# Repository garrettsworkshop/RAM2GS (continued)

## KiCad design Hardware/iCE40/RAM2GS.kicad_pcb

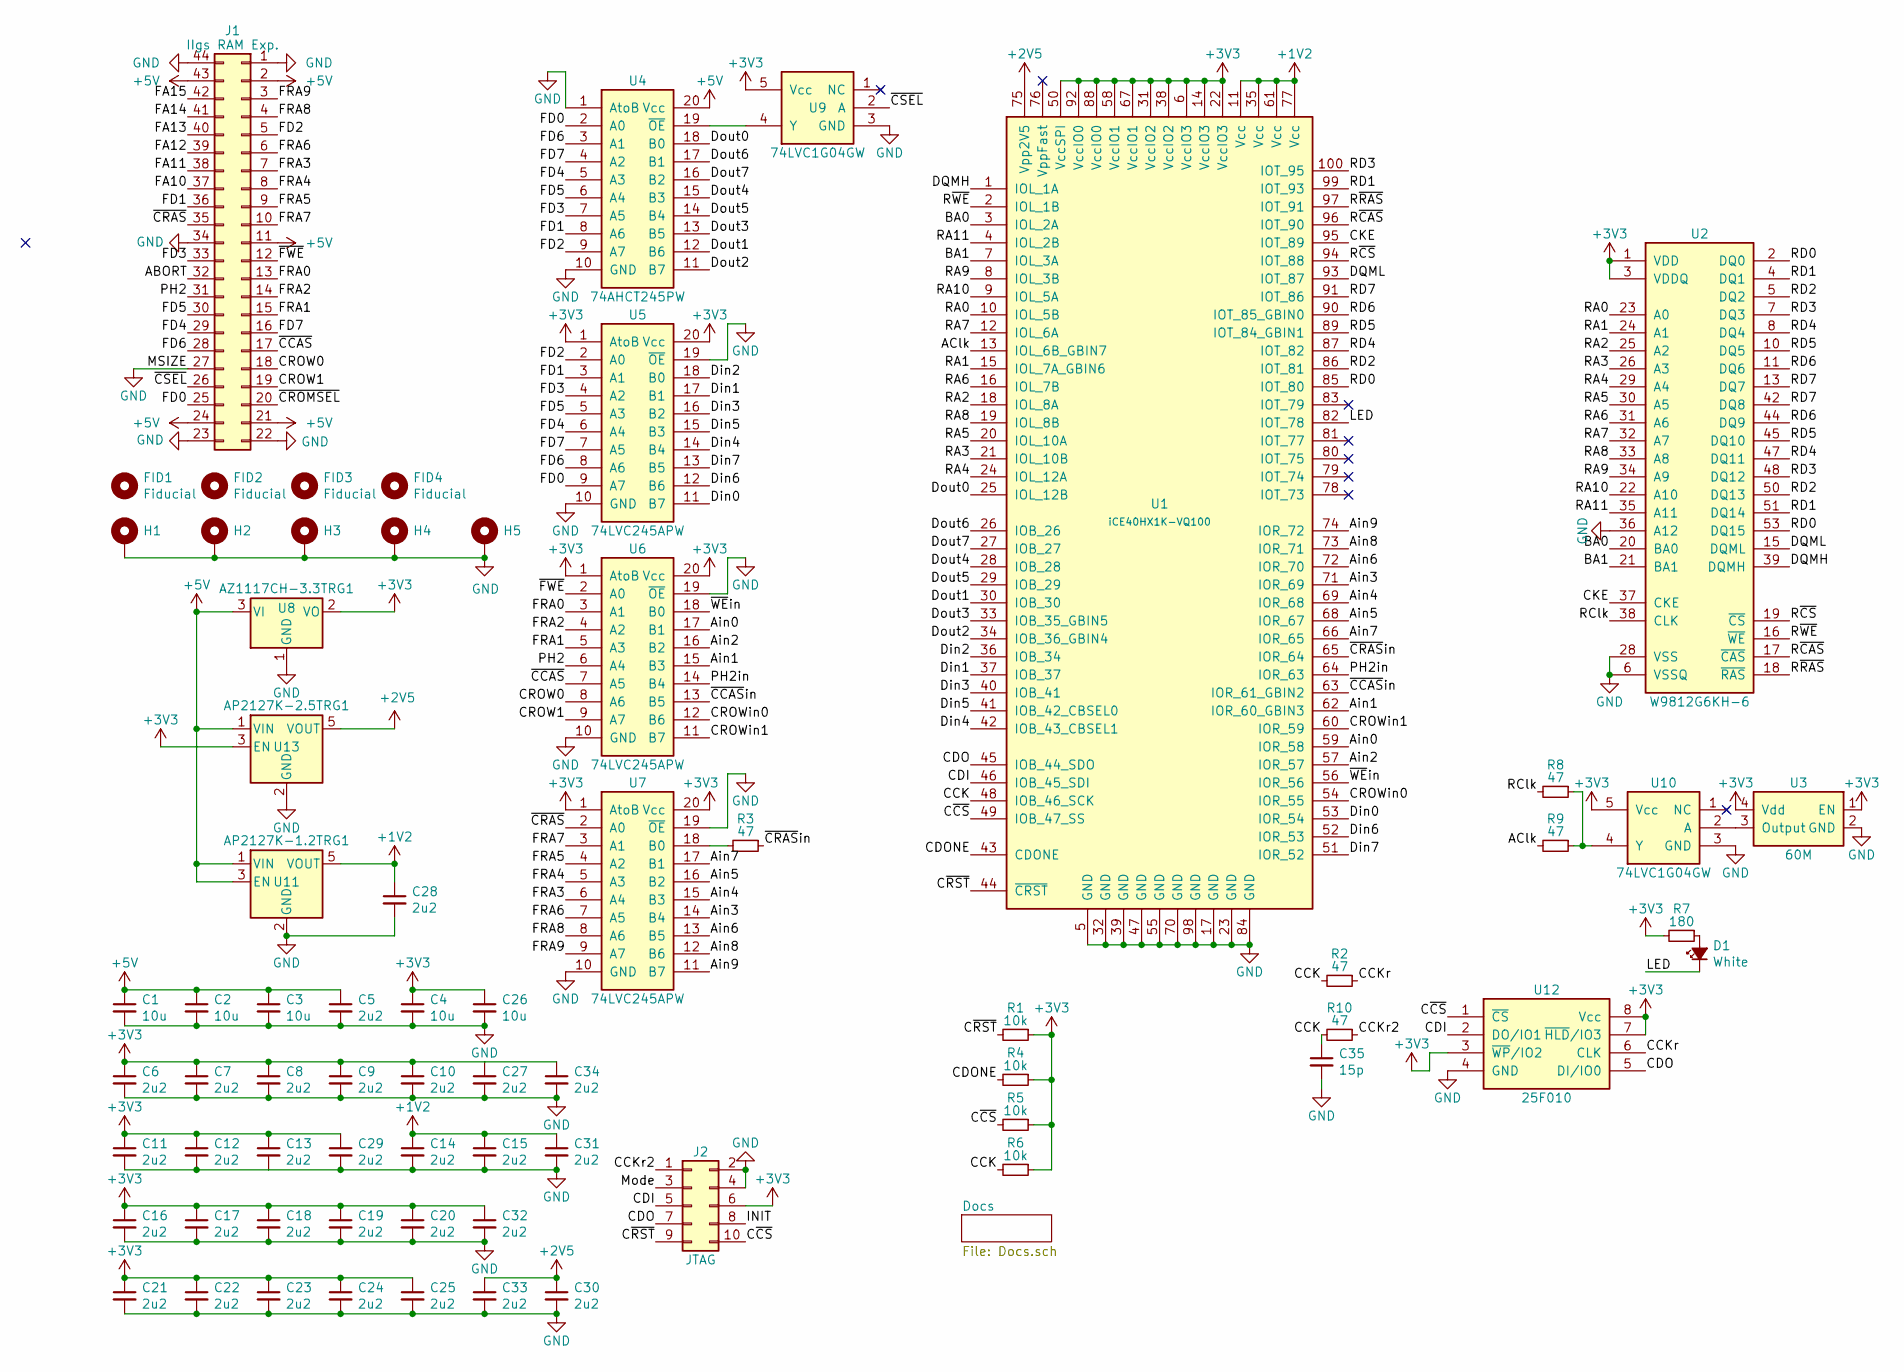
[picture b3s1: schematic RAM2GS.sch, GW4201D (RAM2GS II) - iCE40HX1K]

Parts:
C1, C2, C3, C4, C26: 10u; C_0805; Mfg. Part Numbers Samsung CL21A106KAYNNNE; LCSC Part C15850
C5, C6, C7, C8, C9, C10, C11, C12, C13, C14, C15, C16, C17, C18, C19, C20, C21, C22, C23, C24, C25, C27, C28, C29, C30, C31, C32, C33, C34: 2u2; C_0603; Mfg. Part Numbers Samsung CL10A225KO8NNNC; LCSC Part C23630
C35: 15p; C_0603; Mfg. Part Numbers Samsung CL10C150JB8NNNC; LCSC Part C1644
D1: White; LED_0805; Mfg. Part Numbers Hubei Kento C34499; LCSC Part C34499
FID1, FID2, FID3, FID4: Fiducial
H1, H2, H4, H5: PasteHole_1.152mm_NPTH
H3: PasteHole_1.1mm_PTH
J1: IIgs RAM Exp.; AppleIIgsMemoryExpansion_Edge
J2: JTAG; Tag-Connect_TC2050-IDC-FP_2x05_P1.27mm_Vertical
R1, R4, R5, R6: 10k; R_0603; Mfg. Part Numbers Uniroyal 0603WAF1002T5E; LCSC Part C25804
R2, R3, R8, R9, R10: 47; R_0603; Mfg. Part Numbers Uniroyal 0603WAF470JT5E; LCSC Part C23182
R7: 180; R_0805; Mfg. Part Numbers Uniroyal 0805W8F1800T5E; LCSC Part C25270
U1: iCE40HX1K-VQ100; TQFP-100_14x14mm_P0.5mm; Mfg. Part Numbers Lattice iCE40HX1K-VQ100; LCSC Part C1519043
U2: W9812G6KH-6; TSOP-II-54_22.2x10.16mm_P0.8mm; Mfg. Part Numbers Winbond W9812G6KH-6, Winbond W9812G6KH-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; LCSC Part C62379
U3: 60M; Crystal_SMD_7050-4Pin_7.0x5.0mm_SiTime; Mfg. Part Numbers SiTime SIT1602AI-82-33E-60.000000Y, She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; LCSC Part C26255
U4: 74AHCT245PW; TSSOP-20_4.4x6.5mm_P0.65mm; Mfg. Part Numbers NXP 74AHCT245PW, NXP 74AHCT245APW, TI S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; LCSC Part C173388
U5, U6, U7: 74LVC245APW; TSSOP-20_4.4x6.5mm_P0.65mm; Mfg. Part Numbers NXP 74LVC245APW, TI SN74LVC245APW, NXP 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; LCSC Part C6082
U8: AZ1117CH-3.3TRG1; SOT-223; Mfg. Part Numbers Diodes AZ1117CH-3.3TRG1, Diodes AZ1117E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; LCSC Part C92102
U9, U10: 74LVC1G04GW; SOT-353; Mfg. Part Numbers NXP 74LVC1G04GW, TI SN74LVC1G04DCK; LCSC Part C10237
U11: AP2127K-1.2TRG1; SOT-23-5; Mfg. Part Numbers Diodes AP2127K-1.2TRG1, Torex XC6228D12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; LCSC Part C151376
U12: 25F010; SOIC-8_3.9mm; Mfg. Part Numbers Zetta ZD25WD20BTIGT, Adesto AT25SF081-S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; LCSC Part C2687406
U13: AP2127K-2.5TRG1; SOT-23-5; Mfg. Part Numbers Diodes AP2127K-2.5TRG1, Torex XC6206J25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; LCSC Part C460326

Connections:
+1V2: C14.1, C15.1, C28.1, C31.1, U1.11 (Vcc), U1.35 (Vcc), U1.61 (Vcc), U1.77 (Vcc), U11.5 (VOUT)
+2V5: C30.1, C33.1, U1.75 (Vpp2V5), U13.5 (VOUT)
+3V3: C4.1, C6.1, C7.1, C8.1, C9.1, C10.1, C11.1, C12.1, C13.1, C16.1, C17.1, C18.1, C19.1, C20.1, C21.1, C22.1, C23.1, C24.1, C25.1, C26.1, C27.1, C29.1, C32.1, C34.1, J2.6, R1.1, R4.1, R5.1, R6.1, R7.2, U1.6 (VccIO3), U1.14 (VccIO3), U1.22 (VccIO3), U1.31 (VccIO2), U1.38 (VccIO2), U1.50 (VccSPI), U1.58 (VccIO1), U1.67 (VccIO1), U1.88 (VccIO0), U1.92 (VccIO0), U2.1 (VDD), U2.3 (VDDQ), U2.9 (VDDQ), U2.14 (VDD), U2.27 (VDD), U2.43 (VDDQ), U2.49 (VDDQ), U3.1 (EN), U3.4 (Vdd), U5.1 (AtoB), U5.20 (Vcc), U6.1 (AtoB), U6.20 (Vcc), U7.1 (AtoB), U7.20 (Vcc), U8.2 (VO), U9.5 (Vcc), U10.5 (Vcc), U12.3 (~WP~/IO2), U12.7 (~HLD~/IO3), U12.8 (Vcc), U13.3 (EN)
+5V: C1.1, C2.1, C3.1, C5.1, J1.2, J1.11, J1.21, J1.24, J1.43, U4.20 (Vcc), U8.3 (VI), U11.1 (VIN), U11.3 (EN), U13.1 (VIN)
/ABORT: J1.32
/AClk: R9.2, U1.13 (IOL_6B_GBIN7)
/Ain0: U1.59 (IOR_58), U6.17 (B1)
/Ain1: U1.62 (IOR_60_GBIN3), U6.15 (B3)
/Ain2: U1.57 (IOR_57), U6.16 (B2)
/Ain3: U1.71 (IOR_69), U7.14 (B4)
/Ain4: U1.69 (IOR_68), U7.15 (B3)
/Ain5: U1.68 (IOR_67), U7.16 (B2)
/Ain6: U1.72 (IOR_70), U7.13 (B5)
/Ain7: U1.66 (IOR_65), U7.17 (B1)
/Ain8: U1.73 (IOR_71), U7.12 (B6)
/Ain9: U1.74 (IOR_72), U7.11 (B7)
/BA0: U1.3 (IOL_2A), U2.20 (BA0)
/BA1: U1.7 (IOL_3A), U2.21 (BA1)
/CCK: C35.1, R2.2, R6.2, R10.2, U1.48 (IOB_46_SCK)
/CCKr: R2.1, U12.6 (CLK)
/CCKr2: J2.1, R10.1
/CDI: J2.5, U1.46 (IOB_45_SDI), U12.2 (DO/IO1)
/CDO: J2.7, U1.45 (IOB_44_SDO), U12.5 (DI/IO0)
/CDONE: R4.2, U1.43 (CDONE)
/CKE: U1.95 (IOT_89), U2.37 (CKE)
/CROW0: J1.18, U6.8 (A6)
/CROW1: J1.19, U6.9 (A7)
/CROWin0: U1.54 (IOR_55), U6.12 (B6)
/CROWin1: U1.60 (IOR_59), U6.11 (B7)
/C~CS~: J2.10, R5.2, U1.49 (IOB_47_SS), U12.1 (~CS~)
/C~RST~: J2.9, R1.2, U1.44 (~CRST~)
/DQMH: U1.1 (IOL_1A), U2.39 (DQMH)
/DQML: U1.93 (IOT_87), U2.15 (DQML)
/Din0: U1.53 (IOR_54), U5.11 (B7)
/Din1: U1.37 (IOB_37), U5.17 (B1)
/Din2: U1.36 (IOB_34), U5.18 (B0)
/Din3: U1.40 (IOB_41), U5.16 (B2)
/Din4: U1.42 (IOB_43_CBSEL1), U5.14 (B4)
/Din5: U1.41 (IOB_42_CBSEL0), U5.15 (B3)
/Din6: U1.52 (IOR_53), U5.12 (B6)
/Din7: U1.51 (IOR_52), U5.13 (B5)
/Dout0: U1.25 (IOL_12B), U4.18 (B0)
/Dout1: U1.30 (IOB_30), U4.12 (B6)
/Dout2: U1.34 (IOB_36_GBIN4), U4.11 (B7)
/Dout3: U1.33 (IOB_35_GBIN5), U4.13 (B5)
/Dout4: U1.28 (IOB_28), U4.15 (B3)
/Dout5: U1.29 (IOB_29), U4.14 (B4)
/Dout6: U1.26 (IOB_26), U4.17 (B1)
/Dout7: U1.27 (IOB_27), U4.16 (B2)
/FA10: J1.37
/FA11: J1.38
/FA12: J1.39
/FA13: J1.40
/FA14: J1.41
/FA15: J1.42
/FD0: J1.25, U4.2 (A0), U5.9 (A7)
/FD1: J1.36, U4.8 (A6), U5.3 (A1)
/FD2: J1.5, U4.9 (A7), U5.2 (A0)
/FD3: J1.33, U4.7 (A5), U5.4 (A2)
/FD4: J1.29, U4.5 (A3), U5.6 (A4)
/FD5: J1.30, U4.6 (A4), U5.5 (A3)
/FD6: J1.28, U4.3 (A1), U5.8 (A6)
/FD7: J1.16, U4.4 (A2), U5.7 (A5)
/FRA0: J1.13, U6.3 (A1)
/FRA1: J1.15, U6.5 (A3)
/FRA2: J1.14, U6.4 (A2)
/FRA3: J1.7, U7.6 (A4)
/FRA4: J1.8, U7.5 (A3)
/FRA5: J1.9, U7.4 (A2)
/FRA6: J1.6, U7.7 (A5)
/FRA7: J1.10, U7.3 (A1)
/FRA8: J1.4, U7.8 (A6)
/FRA9: J1.3, U7.9 (A7)
/INIT: J2.8
/LED: D1.1 (K), U1.82 (IOT_78)
/Mode: J2.3
/PH2: J1.31, U6.6 (A4)
/PH2in: U1.64 (IOR_63), U6.14 (B4)
/RA0: U1.10 (IOL_5B), U2.23 (A0)
/RA1: U1.15 (IOL_7A_GBIN6), U2.24 (A1)
/RA2: U1.18 (IOL_8A), U2.25 (A2)
/RA3: U1.21 (IOL_10B), U2.26 (A3)
/RA4: U1.24 (IOL_12A), U2.29 (A4)
/RA5: U1.20 (IOL_10A), U2.30 (A5)
/RA6: U1.16 (IOL_7B), U2.31 (A6)
/RA7: U1.12 (IOL_6A), U2.32 (A7)
/RA8: U1.19 (IOL_8B), U2.33 (A8)
/RA9: U1.8 (IOL_3B), U2.34 (A9)
/RA10: U1.9 (IOL_5A), U2.22 (A10)
/RA11: U1.4 (IOL_2B), U2.35 (A11)
/RClk: R8.2, U2.38 (CLK)
/RD0: U1.85 (IOT_80), U2.2 (DQ0), U2.53 (DQ15)
/RD1: U1.99 (IOT_93), U2.4 (DQ1), U2.51 (DQ14)
/RD2: U1.86 (IOT_81), U2.5 (DQ2), U2.50 (DQ13)
/RD3: U1.100 (IOT_95), U2.7 (DQ3), U2.48 (DQ12)
/RD4: U1.87 (IOT_82), U2.8 (DQ4), U2.47 (DQ11)
/RD5: U1.89 (IOT_84_GBIN1), U2.10 (DQ5), U2.45 (DQ10)
/RD6: U1.90 (IOT_85_GBIN0), U2.11 (DQ6), U2.44 (DQ9)
/RD7: U1.91 (IOT_86), U2.13 (DQ7), U2.42 (DQ8)
/R~CAS~: U1.96 (IOT_90), U2.17 (~CAS~)
/R~CS~: U1.94 (IOT_88), U2.19 (~CS~)
/R~RAS~: U1.97 (IOT_91), U2.18 (~RAS~)
/R~WE~: U1.2 (IOL_1B), U2.16 (~WE~)
/~CCAS~: J1.17, U6.7 (A5)
/~CCAS~in: U1.63 (IOR_61_GBIN2), U6.13 (B5)
/~CRAS~: J1.35, U7.2 (A0)
/~CRAS~in: R3.1, U1.65 (IOR_64)
/~CROMSEL~: J1.20
/~CSEL~: J1.26, U9.2 (A)
/~FWE~: J1.12, U6.2 (A0)
/~WE~in: U1.56 (IOR_56), U6.18 (B0)
GND: C1.2, C2.2, C3.2, C4.2, C5.2, C6.2, C7.2, C8.2, C9.2, C10.2, C11.2, C12.2, C13.2, C14.2, C15.2, C16.2, C17.2, C18.2, C19.2, C20.2, C21.2, C22.2, C23.2, C24.2, C25.2, C26.2, C27.2, C28.2, C29.2, C30.2, C31.2, C32.2, C33.2, C34.2, C35.2, H1.1, H2.1, H3.1, H4.1, H5.1, J1.1, J1.22, J1.23, J1.27, J1.34, J1.44, J2.2, J2.4, U1.5 (GND), U1.17 (GND), U1.23 (GND), U1.32 (GND), U1.39 (GND), U1.47 (GND), U1.55 (GND), U1.70 (GND), U1.84 (GND), U1.98 (GND), U2.6 (VSSQ), U2.12 (VSSQ), U2.28 (VSS), U2.36 (A12), U2.41 (VSS), U2.46 (VSSQ), U2.52 (VSSQ), U2.54 (VSS), U3.2 (GND), U4.1 (AtoB), U4.10 (GND), U5.10 (GND), U5.19 (~OE~), U6.10 (GND), U6.19 (~OE~), U7.10 (GND), U7.19 (~OE~), U8.1 (GND), U9.3 (GND), U10.3 (GND), U11.2 (GND), U12.4 (GND), U13.2 (GND)
unnamed: D1.2 (A), R7.1
unnamed: R3.2, U7.18 (B0)
unnamed: R8.1, R9.1, U10.4 (Y)
unnamed: U4.19 (~OE~), U9.4 (Y)
unnamed: U3.3 (Output), U10.2 (A)

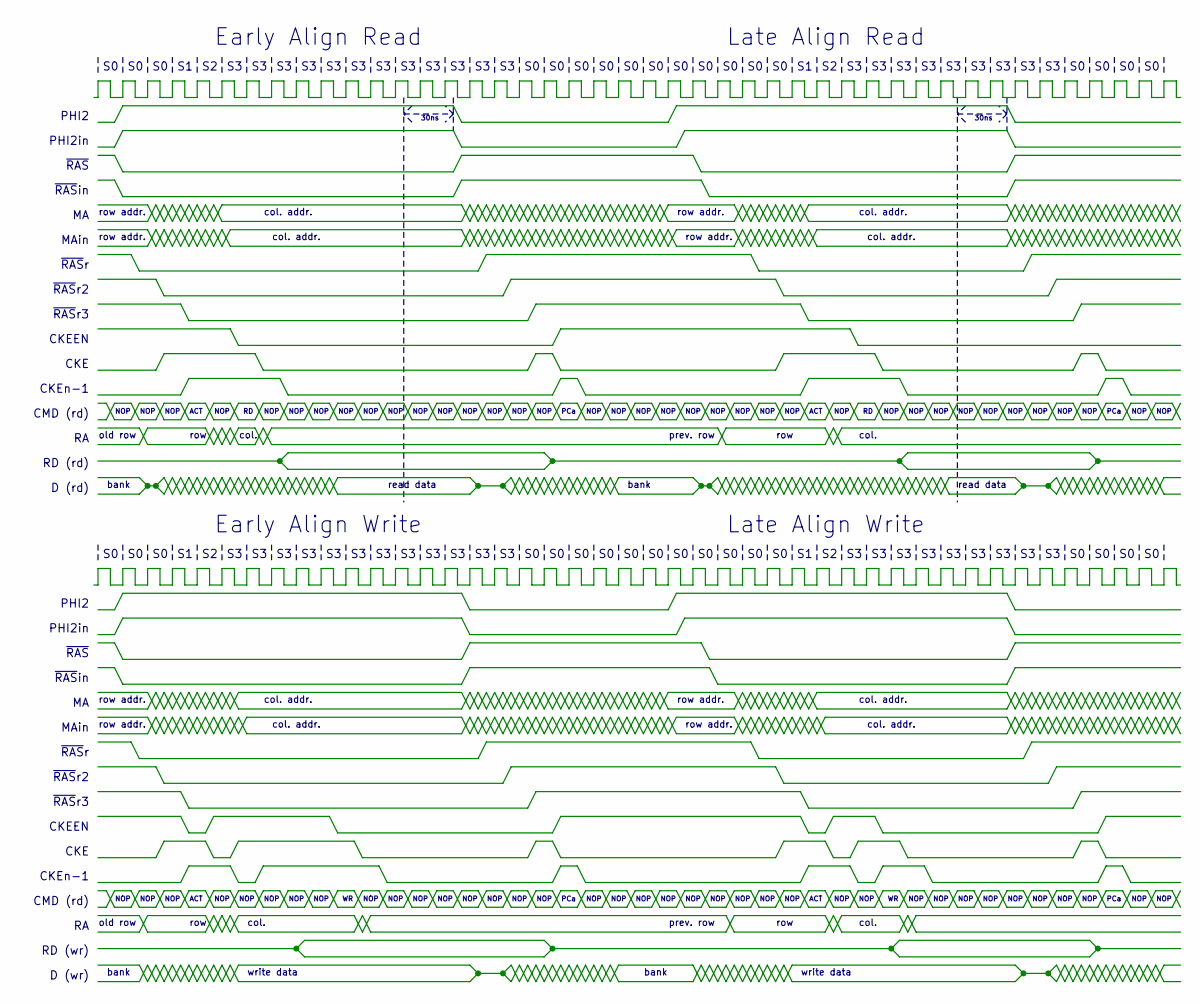
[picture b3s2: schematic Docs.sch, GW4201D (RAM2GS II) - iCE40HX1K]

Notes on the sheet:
Early Align Read
Late Align Read
30ns
PHI2
PHI2in
row addr.
col. addr.
MAin
~RAS~
~RAS~in
~RAS~r
CKE
NOP
CKEEN
prev. row
row
col.
old row
bank
read data
D (rd)
RD (rd)
CMD (rd)
ACT
PCa
RD (wr)
D (wr)
write data
Late Align Write
Early Align Write
~RAS~r2
CKEn-1
~RAS~r3

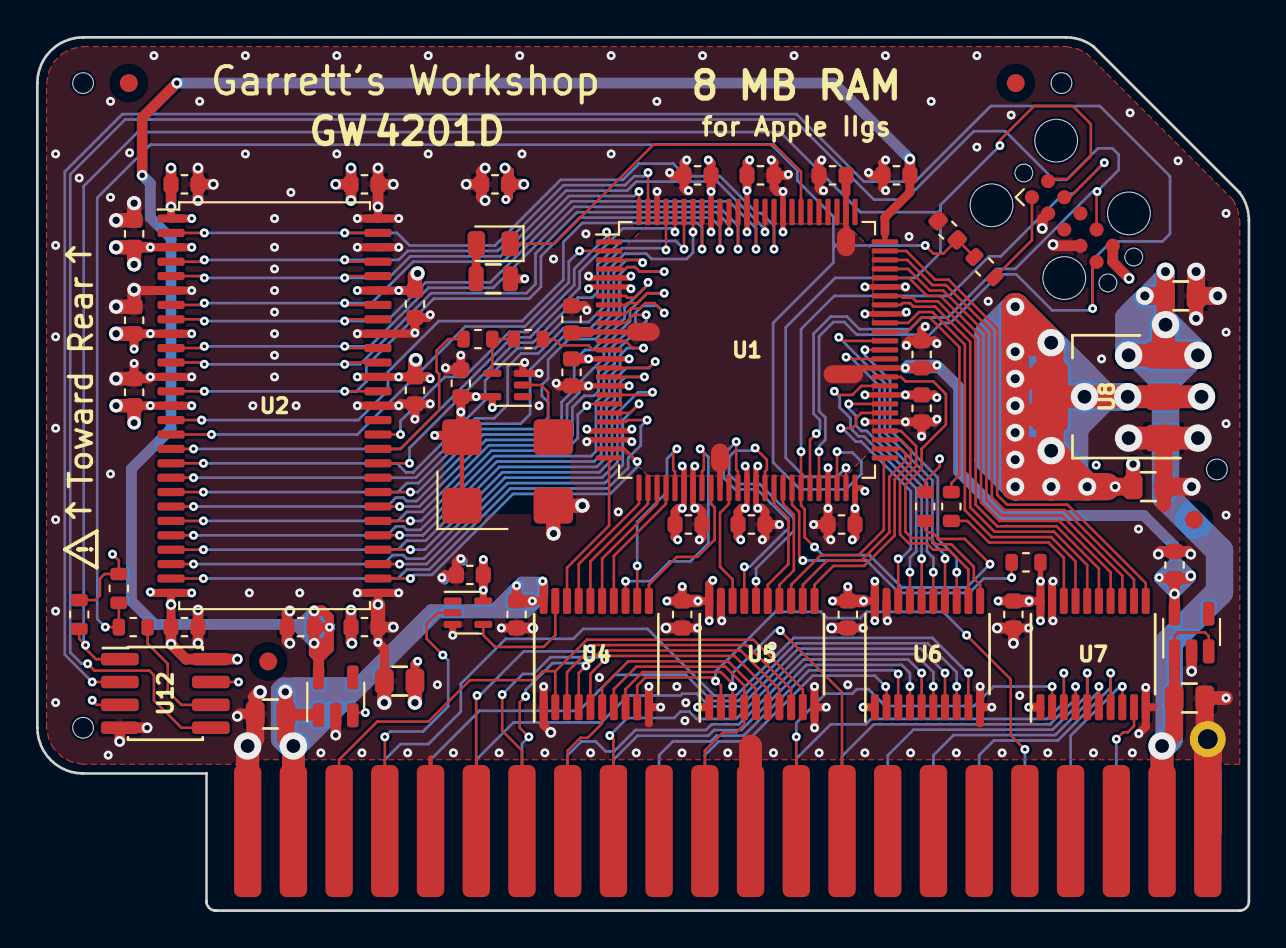
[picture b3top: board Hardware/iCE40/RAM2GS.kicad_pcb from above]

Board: 4 copper layers, 67.3 x 48.5 mm, 70 parts (0 on the bottom side), 107 nets.

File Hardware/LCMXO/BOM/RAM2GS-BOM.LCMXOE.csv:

Reference, Quantity, Value, Footprint, Datasheet, Notes, LCSC Part, Mfg. Part Numbers
C30 ,1,15p,stdpads:C_0603,,"10V or higher. Any manufacturer's part is acceptable but Samsung, Murata, Yageo preferred.",C1644,Samsung CL10C150JB8NNNC
C1 C2 C3 C4 C26 ,5,10u,stdpads:C_0805,,"10V or higher. Any manufacturer's part is acceptable but Samsung, Murata, Yageo preferred.",C15850,Samsung CL21A106KAYNNNE
C5 C6 C7 C8 C9 C10 C11 C12 C13 C14 C15 C16 C17 C18 C19 C20 C21 C22 C23 C24 C25 C27 C28 C29 ,24,2u2,stdpads:C_0603,,"10V or higher. Any manufacturer's part is acceptable but Samsung, Murata, Yageo preferred.",C23630,Samsung CL10A225KO8NNNC
D1 ,1,Amber,stdpads:LED_0805,,Any manufacturer's part is acceptable.,,
FID1 FID2 FID3 FID4 ,4,Fiducial,stdpads:Fiducial,,DNP - SMT vision system fiducial,,
H1 H2 H4 H5 ,4, ,stdpads:PasteHole_1.152mm_NPTH,,DNP - mounting hole for solder paste printing,,
H3 ,1, ,stdpads:PasteHole_1.1mm_PTH,,DNP - mounting hole,,
J1 ,1,IIgs RAM Exp.,stdpads:AppleIIgsMemoryExpansion_Edge,,DNP - edge connector,,
J2 ,1,JTAG,Connector:Tag-Connect_TC2050-IDC-FP_2x05_P1.27mm_Vertical,,DNP - test pad connector,,
R1 R2 ,2,22k,stdpads:R_0805,,Any manufacturer's part is acceptable.,C17560,Uniroyal 0805W8F2202T5E
R4 ,1,DNP,stdpads:R_0805,,,,
R3 R5 R6 R7 ,4,47,stdpads:R_0603,,Any manufacturer's part is acceptable.,C23182,Uniroyal 0603WAF470JT5E
R8 ,1,220,stdpads:R_0805,,Any manufacturer's part is acceptable.,C17557,Uniroyal 0805W8F2200T5E
U1 ,1,LCMXO256E-TN100,stdpads:TQFP-100_14x14mm_P0.5mm,,,C1550734,"Lattice LCMXO256E-3TN100C, Lattice LCMXO256E-4TN100C, Lattice LCMXO256E-5TN100C, Lattice LCMXO256E-3TN100I, Lattice LCMXO256E-4TN100I, Lattice LCMXO640E-3TN100C, Lattice LCMXO640E-4TN100C, Lattice LCMXO640E-5TN100C, Lattice LCMXO640E-3TN100I, Lattice LCMXO640E-4TN100I"
U9 U10 ,2,74LVC1G04GW,stdpads:SOT-353,,Most 74LVC1G04 or 74AHC1G04 in SOT-353 package is acceptable.,C10237,"NXP 74LVC1G04GW, TI SN74LVC1G04DCK, NXP 74AHC1G04GW, TI SN74AHC1G04DCK"
U11 ,1,AP2127K-1.2TRG1,stdpads:SOT-23-5,,Most 1.2V regulator in SOT-23-5 package is acceptable.,C151376,"Diodes AP2127K-1.2TRG1, Torex XC6228D122VR"
U12 ,1,25F010,stdpads:SOIC-8_3.9mm,,Most SPI flash in SOIC-8 (3.9mm / 150 mil width) package is acceptable.,C2687406,"Zetta ZD25WD20BTIGT, Adesto AT25SF081-SSHD, Winbond W25X20CLSNIG"
U2 ,1,W9812G6KH-6,stdpads:TSOP-II-54_22.2x10.16mm_P0.8mm,,Most 166 MHz 128/256 Mbit x16 SDRAM is acceptable.,C62379,"Winbond W9812G6KH-6, Winbond W9812G6KH-6I, Winbond W9825G6KH-6, Winbond W9825G6KH-6I, ISSI IS42S16160J-6TL, ISSI IS42S16160J-6TLI, Micron MT48LC16M16A2P-6A :G, Micron MT48LC16M16A2P-6A IT:G"
U3 ,1,60M,stdpads:Crystal_SMD_7050-4Pin_7.0x5.0mm_SiTime,,Most 60-62.5 MHz 3.3V crystal oscillator or silicon oscillator is acceptable. Do not use crystal resonator or ceramic resonator.,C26255,"SiTime SIT1602AI-82-33E-60.000000Y, Shenzhen SCTF S7D60.000000B20F30T, Taiten OCETGLJTNF-60MHZ"
U4 ,1,74AHCT245PW,stdpads:TSSOP-20_4.4x6.5mm_P0.65mm,,Most 74AHCT245 in TSSOP-20 package is acceptable.,C173388,"NXP 74AHCT245PW, NXP 74AHCT245APW, TI SN74AHCT245PW"
U5 U6 U7 ,3,74LVC245APW,stdpads:TSSOP-20_4.4x6.5mm_P0.65mm,,Most 74LVC245 or 74AHC245 in TSSOP-20 package is acceptable.,C6082,"NXP 74LVC245APW, TI SN74LVC245APW, NXP 74AHC245PW, NXP 74AHC245APW, TI SN74AHC245PW"
U8 ,1,AZ1117CH-3.3TRG1,stdpads:SOT-223,,Most 1117-type 3.3V regulator in SOT-223 package is acceptable.,C92102,"Diodes AZ1117CH-3.3TRG1, Diodes AZ1117EH-3.3TRG1"

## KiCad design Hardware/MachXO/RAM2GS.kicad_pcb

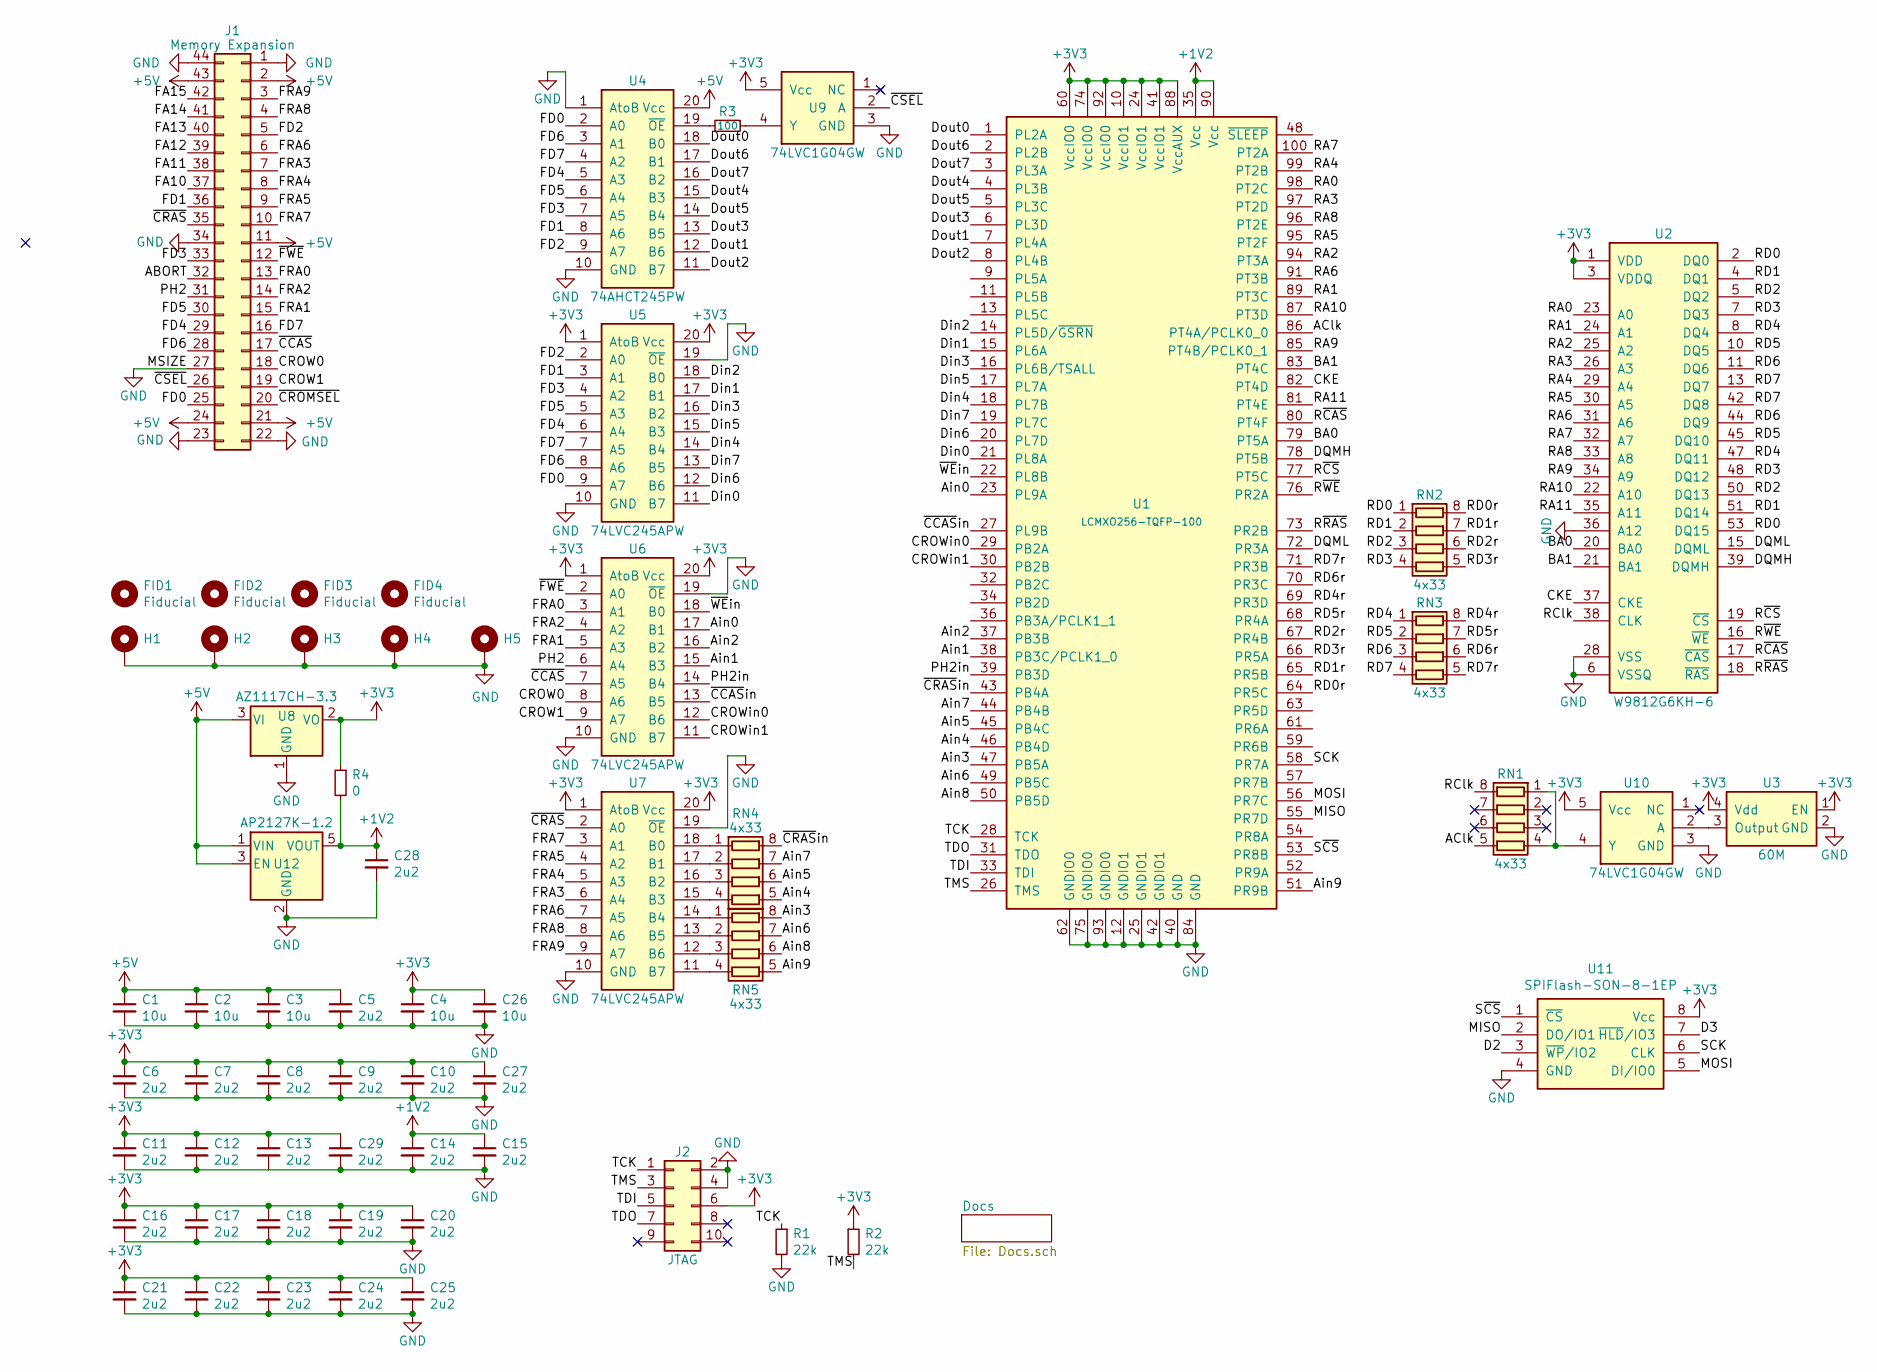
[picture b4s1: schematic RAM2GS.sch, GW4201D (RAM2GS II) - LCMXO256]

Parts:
C1, C2, C3, C4, C26: 10u; C_0805; LCSC Part C15850
C5, C6, C7, C8, C9, C10, C11, C12, C13, C14, C15, C16, C17, C18, C19, C20, C21, C22, C23, C24, C25, C27, C28, C29: 2u2; C_0603; LCSC Part C23630
FID1, FID2, FID3, FID4: Fiducial
H1, H2, H4, H5: PasteHole_1.152mm_NPTH
H3: PasteHole_1.1mm_PTH
J1: Memory Expansion; AppleIIgsMemoryExpansion_Edge
J2: JTAG; Tag-Connect_TC2050-IDC-FP_2x05_P1.27mm_Vertical
R1, R2: 22k; R_0805; LCSC Part C17560
R3: 100; R_0805; LCSC Part C17408
R4: 0; R_0805; LCSC Part C17477
RN1, RN2, RN3, RN4, RN5: 4x33; R4_0402; LCSC Part C25501
U1: LCMXO256-TQFP-100; TQFP-100_14x14mm_P0.5mm
U2: W9812G6KH-6; TSOP-II-54_22.2x10.16mm_P0.8mm; Mfg. Part Numbers Winbond W9812G6KH-6 Winbond W9812G6KH-6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; LCSC Part C62379
U3: 60M; Crystal_SMD_7050-4Pin_7.0x5.0mm_SiTime; Mfg. Part Numbers SiTime SIT1602AI-82-33E-60.000000Y; LCSC Part C26255
U4: 74AHCT245PW; TSSOP-20_4.4x6.5mm_P0.65mm; Mfg. Part Numbers NXP 74AHCT245PW TI SN74AHCT245PW; LCSC Part C173388
U5, U6, U7: 74LVC245APW; TSSOP-20_4.4x6.5mm_P0.65mm; Mfg. Part Numbers NXP 74LVC245APW TI SN74LVC245APW; LCSC Part C6082
U8: AZ1117CH-3.3; SOT-223; Mfg. Part Numbers Diodes AZ1117CH-3.3TR1G Diodes AZ1117EH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; LCSC Part C92102
U9, U10: 74LVC1G04GW; SOT-353; Mfg. Part Numbers NXP 74LVC1G04GW TI SN74LVC1G04DCK; LCSC Part C10237
U11: SPIFlash-SON-8-1EP; SON-8-1EP_3x2mm_P0.5mm_EP0.25x1.65mm
U12: AP2127K-1.2; SOT-23-5

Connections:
+1V2: C14.1, C15.1, C28.1, R4.2, U1.35 (Vcc), U1.90 (Vcc), U12.5 (VOUT)
+3V3: C4.1, C6.1, C7.1, C8.1, C9.1, C10.1, C11.1, C12.1, C13.1, C16.1, C17.1, C18.1, C19.1, C20.1, C21.1, C22.1, C23.1, C24.1, C25.1, C26.1, C27.1, C29.1, J2.6, R2.1, R4.1, U1.10 (VccIO1), U1.24 (VccIO1), U1.41 (VccIO1), U1.60 (VccIO0), U1.74 (VccIO0), U1.88 (VccAUX), U1.92 (VccIO0), U2.1 (VDD), U2.3 (VDDQ), U2.9 (VDDQ), U2.14 (VDD), U2.27 (VDD), U2.43 (VDDQ), U2.49 (VDDQ), U3.1 (EN), U3.4 (Vdd), U5.1 (AtoB), U5.20 (Vcc), U6.1 (AtoB), U6.20 (Vcc), U7.1 (AtoB), U7.20 (Vcc), U8.2 (VO), U9.5 (Vcc), U10.5 (Vcc), U11.8 (Vcc)
+5V: C1.1, C2.1, C3.1, C5.1, J1.2, J1.11, J1.21, J1.24, J1.43, U4.20 (Vcc), U8.3 (VI), U12.1 (VIN), U12.3 (EN)
/ABORT: J1.32
/AClk: RN1.5 (R4.2), U1.86 (PT4A/PCLK0_0)
/Ain0: U1.23 (PL9A), U6.17 (B1)
/Ain1: U1.38 (PB3C/PCLK1_0), U6.15 (B3)
/Ain2: U1.37 (PB3B), U6.16 (B2)
/Ain3: RN5.8 (R1.2), U1.47 (PB5A)
/Ain4: RN4.5 (R4.2), U1.46 (PB4D)
/Ain5: RN4.6 (R3.2), U1.45 (PB4C)
/Ain6: RN5.7 (R2.2), U1.49 (PB5C)
/Ain7: RN4.7 (R2.2), U1.44 (PB4B)
/Ain8: RN5.6 (R3.2), U1.50 (PB5D)
/Ain9: RN5.5 (R4.2), U1.51 (PR9B)
/BA0: U1.79 (PT5A), U2.20 (BA0)
/BA1: U1.83 (PT4C), U2.21 (BA1)
/CKE: U1.82 (PT4D), U2.37 (CKE)
/CROW0: J1.18, U6.8 (A6)
/CROW1: J1.19, U6.9 (A7)
/CROWin0: U1.29 (PB2A), U6.12 (B6)
/CROWin1: U1.30 (PB2B), U6.11 (B7)
/D2: U11.3 (~WP~/IO2)
/D3: U11.7 (~HLD~/IO3)
/DQMH: U1.78 (PT5B), U2.39 (DQMH)
/DQML: U1.72 (PR3A), U2.15 (DQML)
/Din0: U1.21 (PL8A), U5.11 (B7)
/Din1: U1.15 (PL6A), U5.17 (B1)
/Din2: U1.14 (PL5D/~GSRN~), U5.18 (B0)
/Din3: U1.16 (PL6B/TSALL), U5.16 (B2)
/Din4: U1.18 (PL7B), U5.14 (B4)
/Din5: U1.17 (PL7A), U5.15 (B3)
/Din6: U1.20 (PL7D), U5.12 (B6)
/Din7: U1.19 (PL7C), U5.13 (B5)
/Dout0: U1.1 (PL2A), U4.18 (B0)
/Dout1: U1.7 (PL4A), U4.12 (B6)
/Dout2: U1.8 (PL4B), U4.11 (B7)
/Dout3: U1.6 (PL3D), U4.13 (B5)
/Dout4: U1.4 (PL3B), U4.15 (B3)
/Dout5: U1.5 (PL3C), U4.14 (B4)
/Dout6: U1.2 (PL2B), U4.17 (B1)
/Dout7: U1.3 (PL3A), U4.16 (B2)
/FA10: J1.37
/FA11: J1.38
/FA12: J1.39
/FA13: J1.40
/FA14: J1.41
/FA15: J1.42
/FD0: J1.25, U4.2 (A0), U5.9 (A7)
/FD1: J1.36, U4.8 (A6), U5.3 (A1)
/FD2: J1.5, U4.9 (A7), U5.2 (A0)
/FD3: J1.33, U4.7 (A5), U5.4 (A2)
/FD4: J1.29, U4.5 (A3), U5.6 (A4)
/FD5: J1.30, U4.6 (A4), U5.5 (A3)
/FD6: J1.28, U4.3 (A1), U5.8 (A6)
/FD7: J1.16, U4.4 (A2), U5.7 (A5)
/FRA0: J1.13, U6.3 (A1)
/FRA1: J1.15, U6.5 (A3)
/FRA2: J1.14, U6.4 (A2)
/FRA3: J1.7, U7.6 (A4)
/FRA4: J1.8, U7.5 (A3)
/FRA5: J1.9, U7.4 (A2)
/FRA6: J1.6, U7.7 (A5)
/FRA7: J1.10, U7.3 (A1)
/FRA8: J1.4, U7.8 (A6)
/FRA9: J1.3, U7.9 (A7)
/MISO: U1.55 (PR7D), U11.2 (DO/IO1)
/MOSI: U1.56 (PR7C), U11.5 (DI/IO0)
/PH2: J1.31, U6.6 (A4)
/PH2in: U1.39 (PB3D), U6.14 (B4)
/RA0: U1.98 (PT2C), U2.23 (A0)
/RA1: U1.89 (PT3C), U2.24 (A1)
/RA2: U1.94 (PT3A), U2.25 (A2)
/RA3: U1.97 (PT2D), U2.26 (A3)
/RA4: U1.99 (PT2B), U2.29 (A4)
/RA5: U1.95 (PT2F), U2.30 (A5)
/RA6: U1.91 (PT3B), U2.31 (A6)
/RA7: U1.100 (PT2A), U2.32 (A7)
/RA8: U1.96 (PT2E), U2.33 (A8)
/RA9: U1.85 (PT4B/PCLK0_1), U2.34 (A9)
/RA10: U1.87 (PT3D), U2.22 (A10)
/RA11: U1.81 (PT4E), U2.35 (A11)
/RClk: RN1.8 (R1.2), U2.38 (CLK)
/RD0: RN2.1 (R1.1), U2.2 (DQ0), U2.53 (DQ15)
/RD0r: RN2.8 (R1.2), U1.64 (PR5C)
/RD1: RN2.2 (R2.1), U2.4 (DQ1), U2.51 (DQ14)
/RD1r: RN2.7 (R2.2), U1.65 (PR5B)
/RD2: RN2.3 (R3.1), U2.5 (DQ2), U2.50 (DQ13)
/RD2r: RN2.6 (R3.2), U1.67 (PR4B)
/RD3: RN2.4 (R4.1), U2.7 (DQ3), U2.48 (DQ12)
/RD3r: RN2.5 (R4.2), U1.66 (PR5A)
/RD4: RN3.1 (R1.1), U2.8 (DQ4), U2.47 (DQ11)
/RD4r: RN3.8 (R1.2), U1.69 (PR3D)
/RD5: RN3.2 (R2.1), U2.10 (DQ5), U2.45 (DQ10)
/RD5r: RN3.7 (R2.2), U1.68 (PR4A)
/RD6: RN3.3 (R3.1), U2.11 (DQ6), U2.44 (DQ9)
/RD6r: RN3.6 (R3.2), U1.70 (PR3C)
/RD7: RN3.4 (R4.1), U2.13 (DQ7), U2.42 (DQ8)
/RD7r: RN3.5 (R4.2), U1.71 (PR3B)
/R~CAS~: U1.80 (PT4F), U2.17 (~CAS~)
/R~CS~: U1.77 (PT5C), U2.19 (~CS~)
/R~RAS~: U1.73 (PR2B), U2.18 (~RAS~)
/R~WE~: U1.76 (PR2A), U2.16 (~WE~)
/SCK: U1.58 (PR7A), U11.6 (CLK)
/S~CS~: U1.53 (PR8B), U11.1 (~CS~)
/TCK: J2.1, R1.1, U1.28 (TCK)
/TDI: J2.5, U1.33 (TDI)
/TDO: J2.7, U1.31 (TDO)
/TMS: J2.3, R2.2, U1.26 (TMS)
/~CCAS~: J1.17, U6.7 (A5)
/~CCAS~in: U1.27 (PL9B), U6.13 (B5)
/~CRAS~: J1.35, U7.2 (A0)
/~CRAS~in: RN4.8 (R1.2), U1.43 (PB4A)
/~CROMSEL~: J1.20
/~CSEL~: J1.26, U9.2 (A)
/~FWE~: J1.12, U6.2 (A0)
/~WE~in: U1.22 (PL8B), U6.18 (B0)
GND: C1.2, C2.2, C3.2, C4.2, C5.2, C6.2, C7.2, C8.2, C9.2, C10.2, C11.2, C12.2, C13.2, C14.2, C15.2, C16.2, C17.2, C18.2, C19.2, C20.2, C21.2, C22.2, C23.2, C24.2, C25.2, C26.2, C27.2, C28.2, C29.2, H1.1, H2.1, H3.1, H4.1, H5.1, J1.1, J1.22, J1.23, J1.27, J1.34, J1.44, J2.2, J2.4, R1.2, U1.12 (GNDIO1), U1.25 (GNDIO1), U1.40 (GND), U1.42 (GNDIO1), U1.62 (GNDIO0), U1.75 (GNDIO0), U1.84 (GND), U1.93 (GNDIO0), U2.6 (VSSQ), U2.12 (VSSQ), U2.28 (VSS), U2.36 (A12), U2.41 (VSS), U2.46 (VSSQ), U2.52 (VSSQ), U2.54 (VSS), U3.2 (GND), U4.1 (AtoB), U4.10 (GND), U5.10 (GND), U5.19 (~OE~), U6.10 (GND), U6.19 (~OE~), U7.10 (GND), U7.19 (~OE~), U8.1 (GND), U9.3 (GND), U10.3 (GND), U11.4 (GND), U11.9 (GND), U12.2 (GND)
unnamed: R3.1, U9.4 (Y)
unnamed: R3.2, U4.19 (~OE~)
unnamed: RN1.1 (R1.1), RN1.4 (R4.1), U10.4 (Y)
unnamed: RN4.1 (R1.1), U7.18 (B0)
unnamed: RN4.2 (R2.1), U7.17 (B1)
unnamed: RN4.3 (R3.1), U7.16 (B2)
unnamed: RN4.4 (R4.1), U7.15 (B3)
unnamed: RN5.1 (R1.1), U7.14 (B4)
unnamed: RN5.2 (R2.1), U7.13 (B5)
unnamed: RN5.3 (R3.1), U7.12 (B6)
unnamed: RN5.4 (R4.1), U7.11 (B7)
unnamed: U3.3 (Output), U10.2 (A)

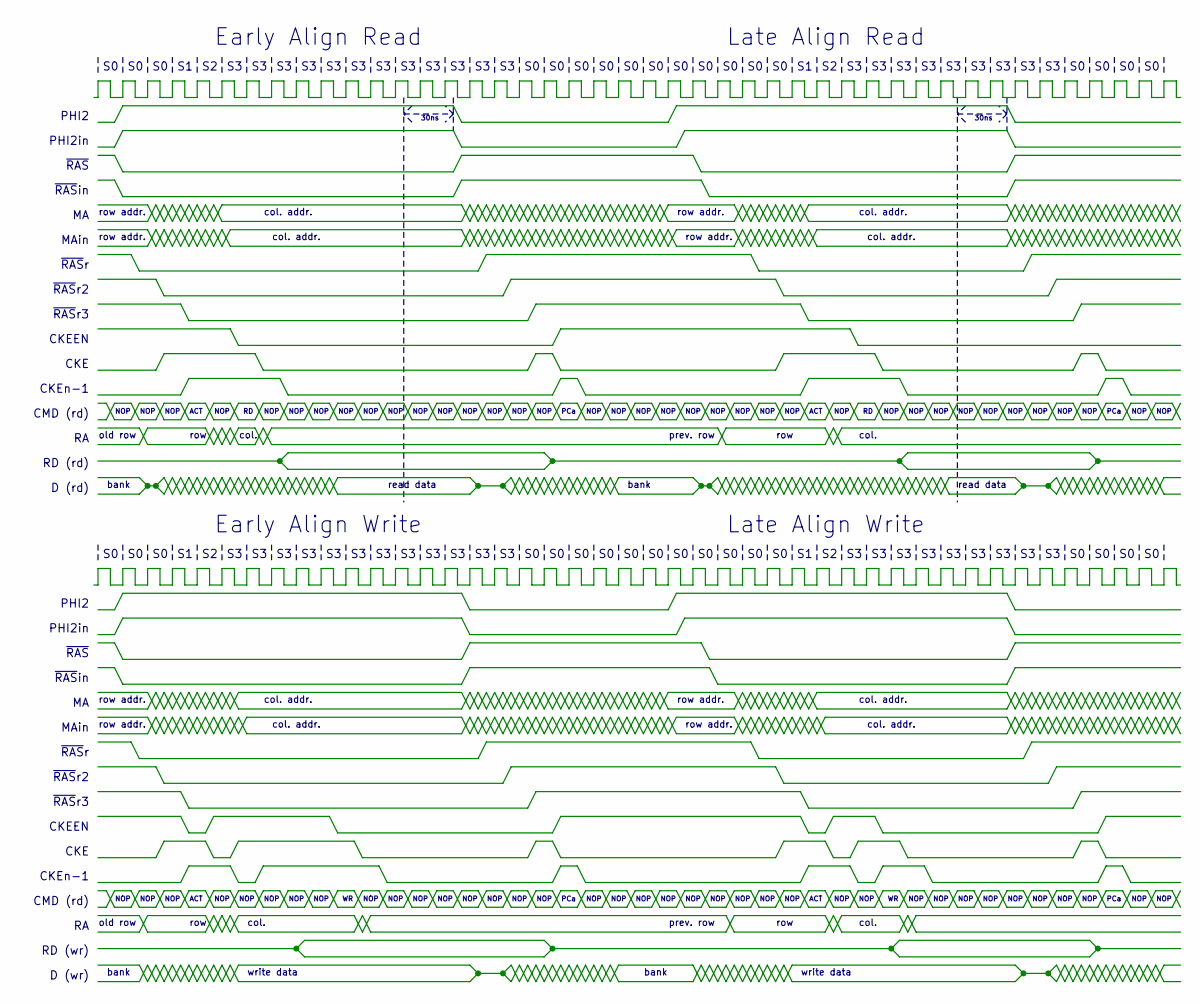
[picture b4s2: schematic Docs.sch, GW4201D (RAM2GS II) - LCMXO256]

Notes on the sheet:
Early Align Read
Late Align Read
30ns
PHI2
PHI2in
row addr.
col. addr.
MAin
~RAS~
~RAS~in
~RAS~r
CKE
NOP
CKEEN
prev. row
row
col.
old row
bank
read data
D (rd)
RD (rd)
CMD (rd)
ACT
PCa
RD (wr)
D (wr)
write data
Late Align Write
Early Align Write
~RAS~r2
CKEn-1
~RAS~r3

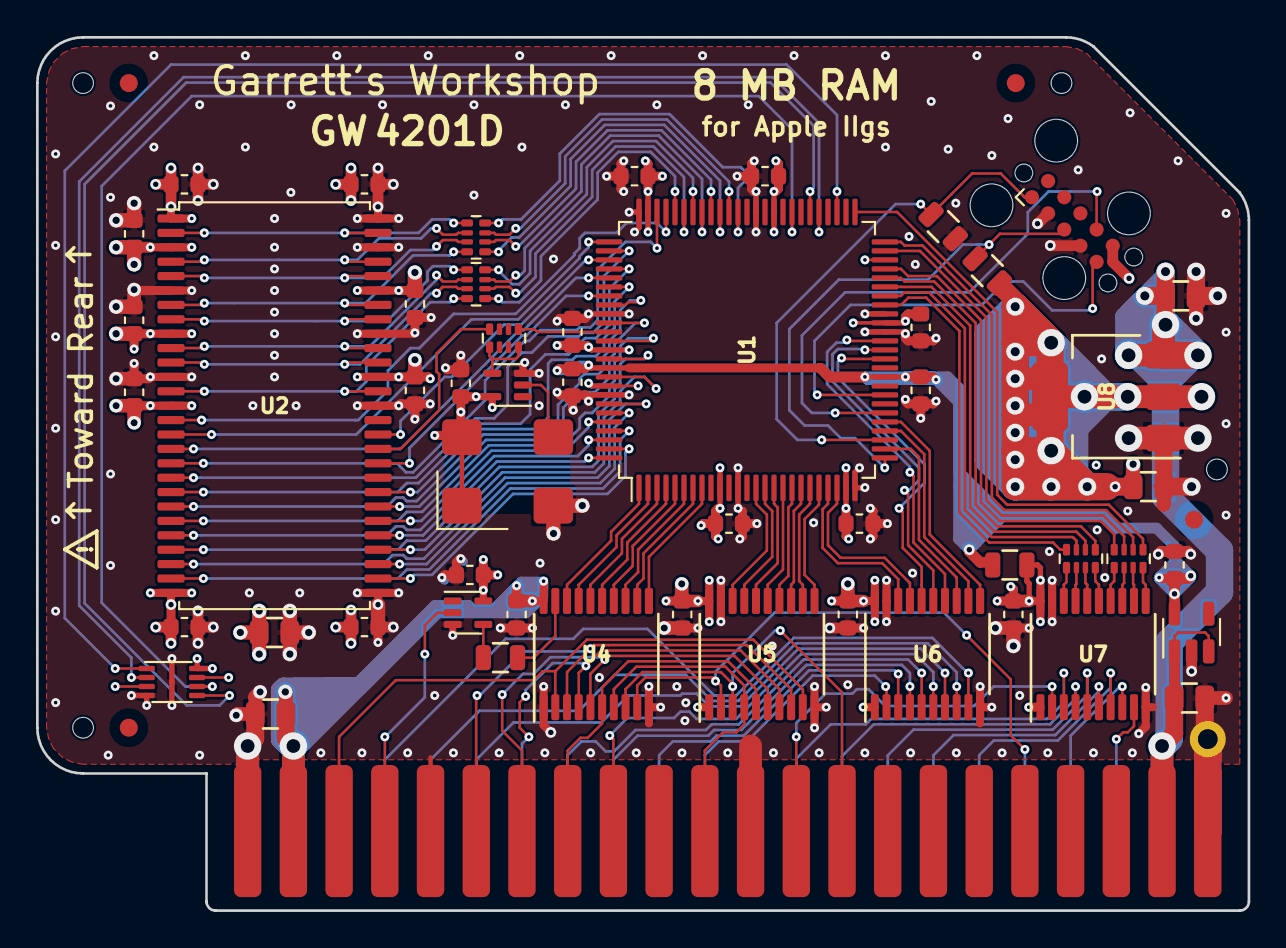
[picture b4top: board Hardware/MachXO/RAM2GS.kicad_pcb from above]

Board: 4 copper layers, 67.3 x 48.5 mm, 61 parts (0 on the bottom side), 120 nets.

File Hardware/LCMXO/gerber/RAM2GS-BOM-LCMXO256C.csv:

Reference, Quantity, Value, Footprint, Datasheet, Notes, LCSC Part, Mfg. Part Numbers
C4 C3 C2 C1 C26 ,5,10u,stdpads:C_0805,,"10V or higher. Any manufacturer's part is acceptable but Samsung, Murata, Yageo preferred.",C15850,Samsung CL21A106KAYNNNE
C5 C25 C24 C23 C22 C21 C20 C19 C18 C17 C16 C15 C14 C13 C12 C11 C10 C9 C8 C7 C6 C27 C28 C29 ,24,2u2,stdpads:C_0603,,"10V or higher. Any manufacturer's part is acceptable but Samsung, Murata, Yageo preferred.",C23630,Samsung CL10A225KO8NNNC
FID1 FID2 FID3 FID4 ,4,Fiducial,stdpads:Fiducial,,DNP - SMT vision system fiducial,,
H1 H2 H4 H5 ,4, ,stdpads:PasteHole_1.152mm_NPTH,,DNP - mounting hole for solder paste printing,,
H3 ,1, ,stdpads:PasteHole_1.1mm_PTH,,DNP - mounting hole,,
J1 ,1,Memory Expansion,stdpads:AppleIIgsMemoryExpansion_Edge,,DNP - edge connector,,
J2 ,1,JTAG,Connector:Tag-Connect_TC2050-IDC-FP_2x05_P1.27mm_Vertical,,DNP - test pad connector,,
R1 R2 ,2,22k,stdpads:R_0805,,Any manufacturer's part is acceptable.,C17560,Uniroyal 0805W8F2202T5E
R3 ,1,100,stdpads:R_0805,,Any manufacturer's part is acceptable.,C17408,Uniroyal 0805W8F1000T5E
R4 ,1,0,stdpads:R_0805,,Any manufacturer's part is acceptable.,C17477,Uniroyal 0805W8F0000T5E
R5 ,1,DNP,stdpads:R_0805,,,,
RN2 RN3 RN5 RN4 RN1 ,5,4x33,stdpads:R4_0402,,Any manufacturer's part is acceptable.,C25501,Uniroyal 4D02WGJ0330TCE
RN6 ,1,4x10k,stdpads:R4_0402,,Any manufacturer's part is acceptable.,C25725,Uniroyal 4D02WGJ0103TCE
U1 ,1,LCMXO256C-3TN100C,stdpads:TQFP-100_14x14mm_P0.5mm,,,C1521848,Lattice LCMXO256C-3TN100C
U10 U9 ,2,74LVC1G04GW,stdpads:SOT-353,,,C10237,"NXP 74LVC1G04GW, TI SN74LVC1G04DCK"
U11 ,1,DNP,stdpads:SOT-23-5,,,,
U12 ,1,25F010,stdpads:SOIC-8_3.9mm,,Most SPI flash in SOIC-8 (3.9mm / 150 mil width) package is acceptale.,,"Zetta ZD25WD20BTIGT, Adesto AT25SF081-SSHD, Winbond W25X20CLSNIG"
U2 ,1,W9812G6KH-6,stdpads:TSOP-II-54_22.2x10.16mm_P0.8mm,,Most 166 MHz 128/256 Mbit SDRAM is acceptable.,C62379,"Winbond W9812G6KH-6 Winbond W9812G6KH-6I, Winbond W9825G6KH-6, Winbond W9825G6KH-6I, ISSI IS42S16160J-6TL, ISSI IS42S16160J-6TLI, Micron MT48LC16M16A2P-6A :G, Micron MT48LC16M16A2P-6A IT:G"
U3 ,1,60M,stdpads:Crystal_SMD_7050-4Pin_7.0x5.0mm_SiTime,,Most 60-62.5 MHz crystal oscillator or silicon oscillator is acceptable. Do not use crystal resonator or ceramic resonator.,C26255,"SiTime SIT1602AI-82-33E-60.000000Y, Shenzhen SCTF S7D60.000000B20F30T, Taiten OCETGLJTNF-60MHZ"
U4 ,1,74AHCT245PW,stdpads:TSSOP-20_4.4x6.5mm_P0.65mm,,,C173388,"NXP 74AHCT245PW, TI SN74AHCT245PW"
U6 U7 U5 ,3,74LVC245APW,stdpads:TSSOP-20_4.4x6.5mm_P0.65mm,,,C6082,"NXP 74LVC245APW, TI SN74LVC245APW"
U8 ,1,AZ1117CH-3.3,stdpads:SOT-223,,Most 1117-type 3.3V regulator in SOT-223 package is acceptable.,C92102,"Diodes AZ1117CH-3.3TRG1, Diodes AZ1117EH-3.3TRG1"
